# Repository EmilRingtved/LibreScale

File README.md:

# LibreScale
## An open source precision scale system
 The project is currently on hold, as I am working on other stuff.

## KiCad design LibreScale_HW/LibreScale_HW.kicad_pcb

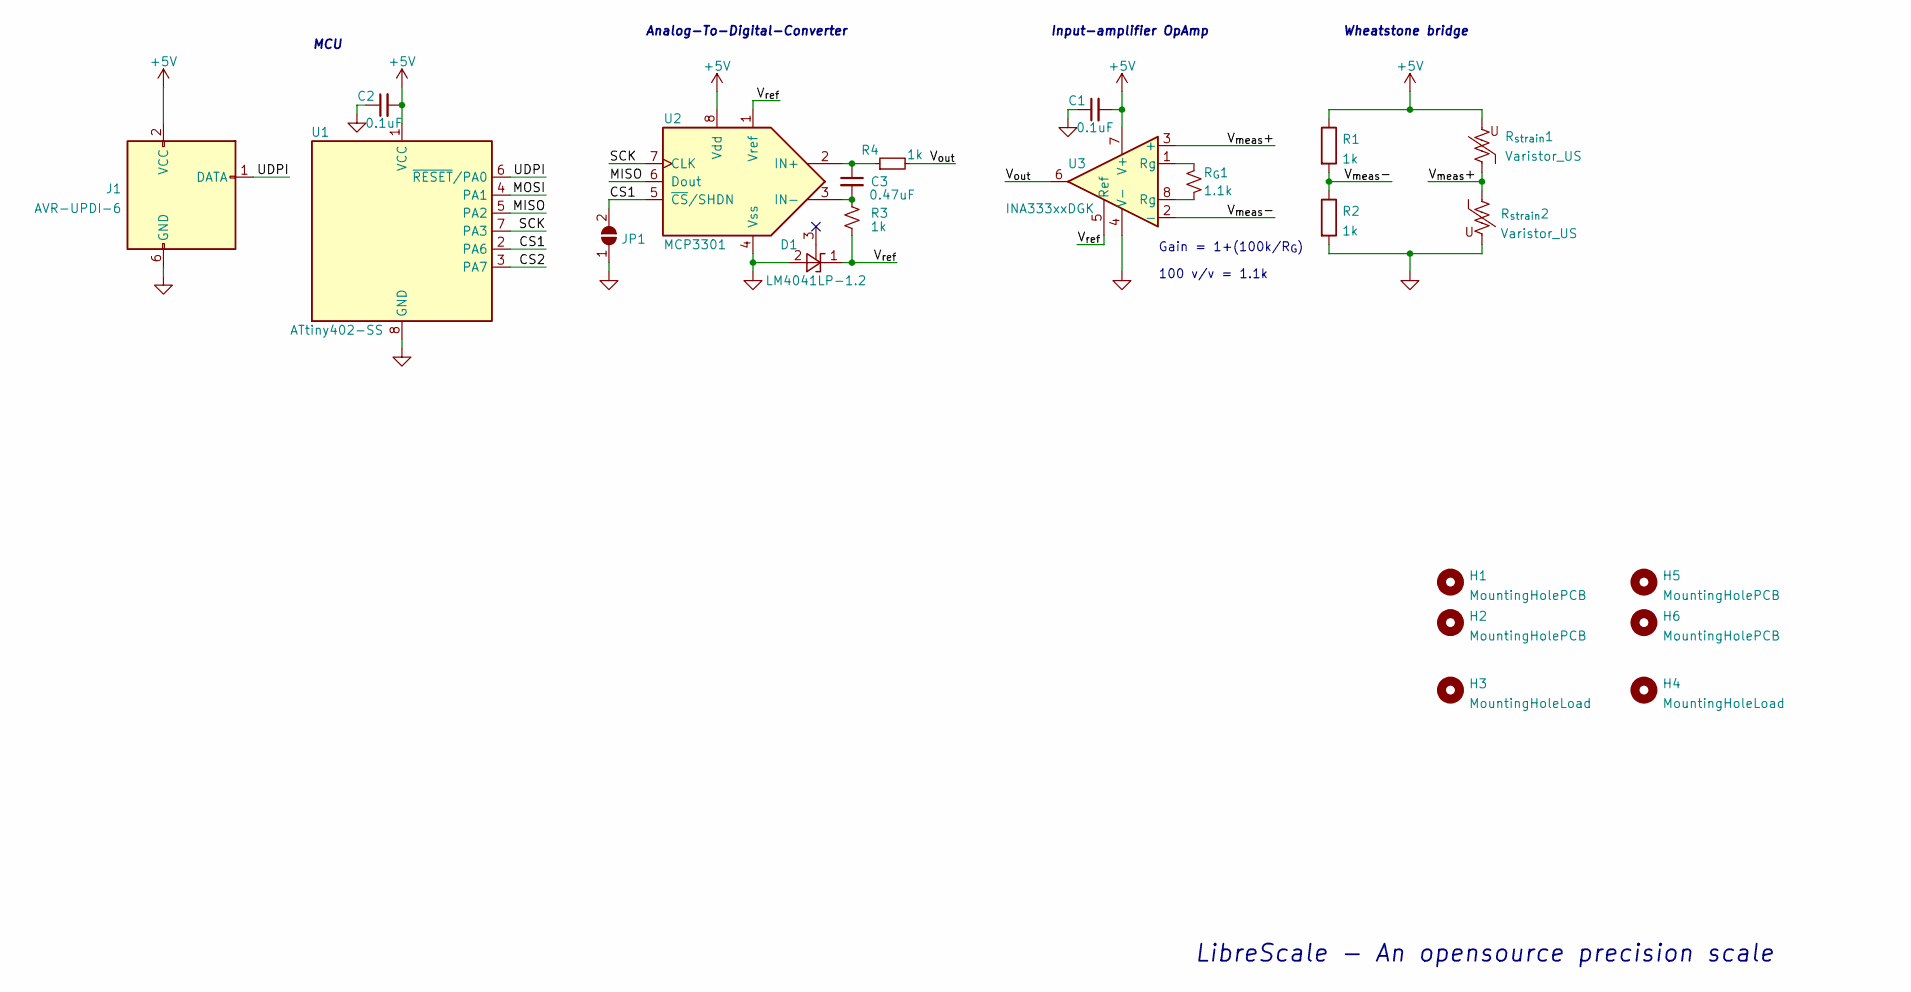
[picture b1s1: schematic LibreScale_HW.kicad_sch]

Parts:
C1, C2: 0.1uF; C_0603_1608Metric
C3: 0.47uF; C_0603_1608Metric
D1: LM4041LP-1.2; SOT-23
H1, H2, H5, H6: MountingHolePCB; MountingHole_3.2mm_M3_Pad
H3, H4: MountingHoleLoad; MountingHole_3.2mm_M3_DIN965_Pad
J1: AVR-UPDI-6; Tag-Connect_TC2030-IDC-NL_2x03_P1.27mm_Vertical
JP1: SolderJumper_2_Open; SolderJumper-2_P1.3mm_Bridged_RoundedPad1.0x1.5mm
R1, R2: 1k; R_0603_1608Metric
R3, R4: 1k; R_0402_1005Metric_Pad0.72x0.64mm_HandSolder
R_{G}1: 1.1k; R_0402_1005Metric_Pad0.72x0.64mm_HandSolder
R_{strain}1, R_{strain}2: Varistor_US; JST_PH_S2B-PH-K_1x02_P2.00mm_Horizontal
U1: ATtiny402-SS; SOIC-8_3.9x4.9mm_P1.27mm
U2: MCP3301; SOIC-8_3.9x4.9mm_P1.27mm
U3: INA333xxDGK; VSSOP-8_3.0x3.0mm_P0.65mm

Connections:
+5V: C1.2, C2.2, J1.2 (VCC), R1.1, R_{strain}1.2, U1.1 (VCC), U2.8 (Vdd), U3.7 (V+)
/CS1: JP1.2 (B), U1.2 (PA6), U2.5 (~CS/SHDN)
/CS2: U1.3 (PA7)
/MISO: U1.5 (PA2), U2.6 (Dout)
/MOSI: U1.4 (PA1)
/SCK: U1.7 (PA3), U2.7 (CLK)
/UDPI: J1.1 (DATA), U1.6 (~RESET/PA0)
/V_{meas}+: R_{strain}1.1, R_{strain}2.1, U3.3 (+)
/V_{meas}-: R1.2, R2.1, U3.2 (-)
/V_{out}: R4.2, U3.6
/V_{ref}: D1.1 (FB), R3.2, U2.1 (Vref), U3.5 (Ref)
GND: C1.1, C2.1, D1.2 (K), J1.6 (GND), JP1.1 (A), R2.2, R_{strain}2.2, U1.8 (GND), U2.4 (Vss), U3.4 (V-)
unnamed: C3.1, R4.1, U2.2 (IN+)
unnamed: C3.2, R3.1, U2.3 (IN-)
unnamed: R_{G}1.1, U3.8 (Rg)
unnamed: R_{G}1.2, U3.1 (Rg)

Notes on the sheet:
100 v/v = 1.1k
Gain = 1+(100k/R_{G})
LibreScale - An opensource precision scale
Wheatstone bridge
Analog-To-Digital-Converter
MCU
Input-amplifier OpAmp

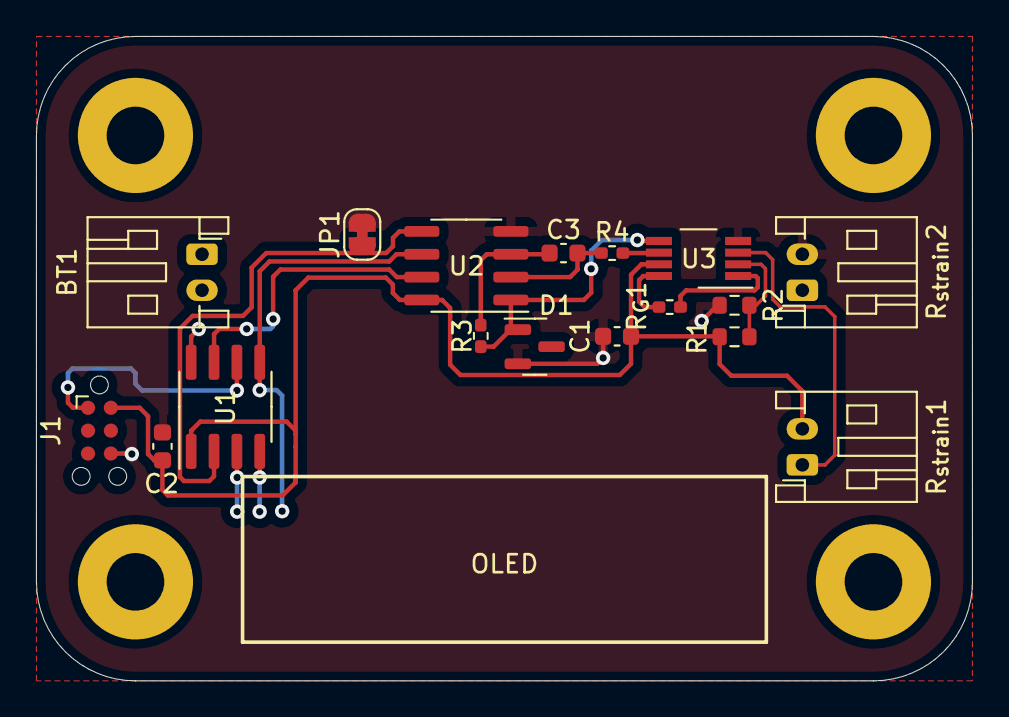
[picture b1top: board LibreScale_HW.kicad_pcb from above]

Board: 2 copper layers, 52.0 x 35.8 mm, 21 parts (0 on the bottom side), 14 nets.

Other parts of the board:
BT1: Battery_Cell; JST_PH_S2B-PH-K_1x02_P2.00mm_Horizontal

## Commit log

2022-02-07 Finished .sch draft
2022-09-28 Minor changes
2022-10-20 minor fixes on PCB
2022-10-22 Routing changes, added parts
